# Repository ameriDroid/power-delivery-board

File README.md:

# Power Delivery board for the Indiedroid Cloud kit

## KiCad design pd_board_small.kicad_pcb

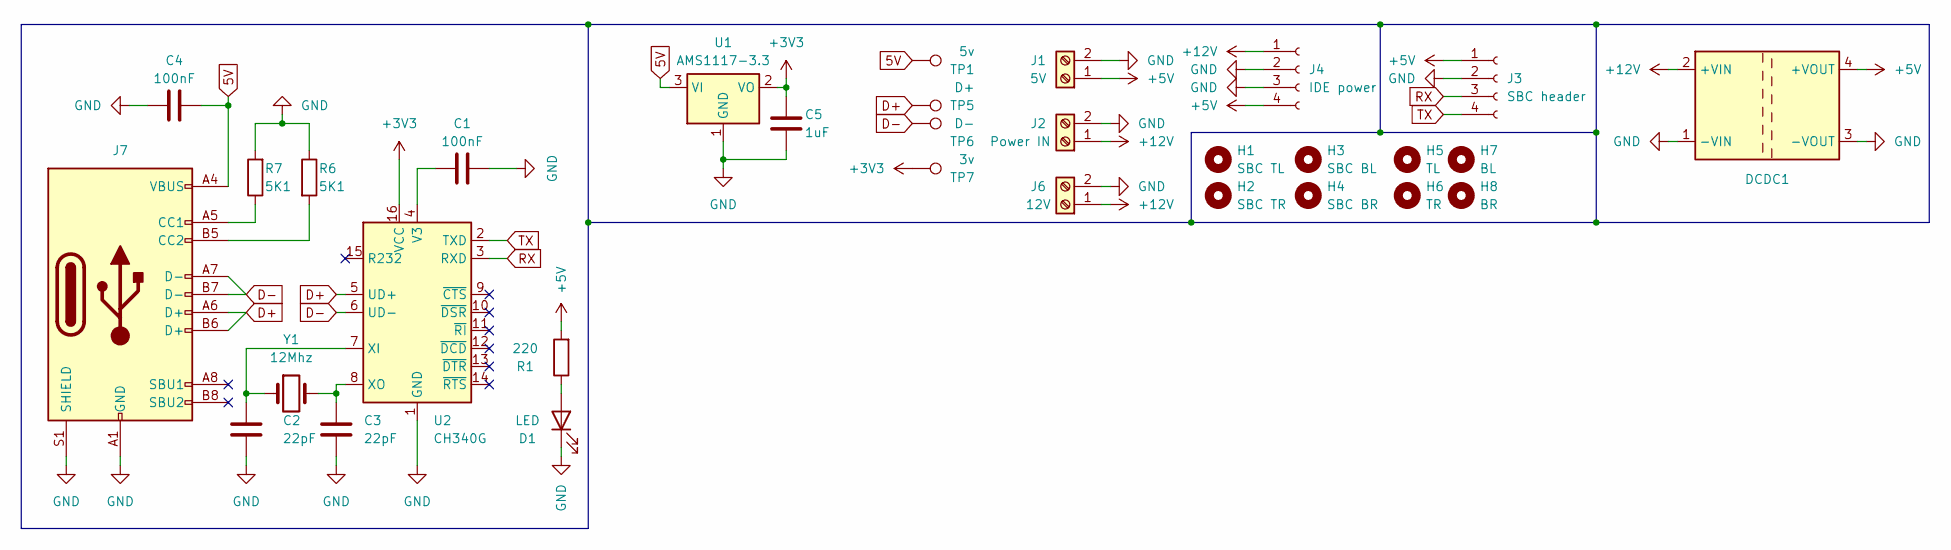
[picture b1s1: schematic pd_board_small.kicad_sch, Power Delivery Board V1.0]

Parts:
C1, C4: 100nF; C_Disc_D3.0mm_W2.0mm_P2.50mm
C2, C3: 22pF; C_Disc_D3.0mm_W2.0mm_P2.50mm
C5: 1uF; C_Disc_D3.0mm_W2.0mm_P2.50mm
D1: LED; LED_D5.0mm
DCDC1: Converter_DCDC_5_32V
H1: SBC TL; MountingHole_3.5mm
H2: SBC TR; MountingHole_3.5mm
H3: SBC BL; MountingHole_3.5mm
H4: SBC BR; MountingHole_3.5mm
H5: TL; MountingHole_3.5mm
H6: TR; MountingHole_3.5mm
H7: BL; MountingHole_3.5mm
H8: BR; MountingHole_3.5mm
J1: 5V; TerminalBlock_RND_205-00001_1x02_P5.00mm_Horizontal
J2: Power IN; TerminalBlock_RND_205-00001_1x02_P5.00mm_Horizontal
J3: SBC header; PinSocket_1x04_P2.54mm_Vertical
J4: IDE power; IDE molex 4pin
J6: 12V; TerminalBlock_RND_205-00001_1x02_P5.00mm_Horizontal
J7: USB_C_Receptacle_USB2.0_16P; USB_C_Receptacle_GCT_USB4105-xx-A_16P_TopMnt_Horizontal
R1: 220; R_Axial_DIN0204_L3.6mm_D1.6mm_P7.62mm_Horizontal
R6, R7: 5K1; R_Axial_DIN0204_L3.6mm_D1.6mm_P7.62mm_Horizontal
TP1: 5v; TestPoint_Pad_D1.5mm
TP5: D+; TestPoint_Pad_D1.5mm
TP6: D-; TestPoint_Pad_D1.5mm
TP7: 3v; TestPoint_Pad_D1.5mm
U1: AMS1117-3.3; SOT-223-3_TabPin2
U2: CH340G; SOIC-16_3.9x9.9mm_P1.27mm
Y1: 12Mhz; Crystal_HC49-4H_Vertical

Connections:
5V: C4.2, J7.A4 (VBUS), J7.A9 (VBUS), J7.B4 (VBUS), J7.B9 (VBUS), TP1.1, U1.3 (VI)
+3V3: C5.1, TP7.1, U1.2 (VO), U2.16 (VCC)
+5V: DCDC1.4 (+VOUT), J1.1, J3.1, J4.4, R1.2
+12V: DCDC1.2 (+VIN), J2.1, J4.1, J6.1
D+: J7.A6 (D+), J7.B6 (D+), TP5.1, U2.5 (UD+)
D-: J7.A7 (D-), J7.B7 (D-), TP6.1, U2.6 (UD-)
GND: C1.2, C2.1, C3.1, C4.1, C5.2, D1.1 (K), DCDC1.1 (-VIN), DCDC1.3 (-VOUT), J1.2, J2.2, J3.2, J4.2, J4.3, J6.2, J7.A1 (GND), J7.A12 (GND), J7.B1 (GND), J7.B12 (GND), J7.S1 (SHIELD), R6.1, R7.2, U1.1 (GND), U2.1 (GND)
unnamed: D1.2 (A), R1.1
unnamed: J7.A5 (CC1), R7.1
unnamed: J7.B5 (CC2), R6.2
unnamed: C1.1, U2.4 (V3)
unnamed: C2.2, U2.7 (XI), Y1.1
unnamed: C3.2, U2.8 (XO), Y1.2
RX: J3.3, U2.3 (RXD)
TX: J3.4, U2.2 (TXD)

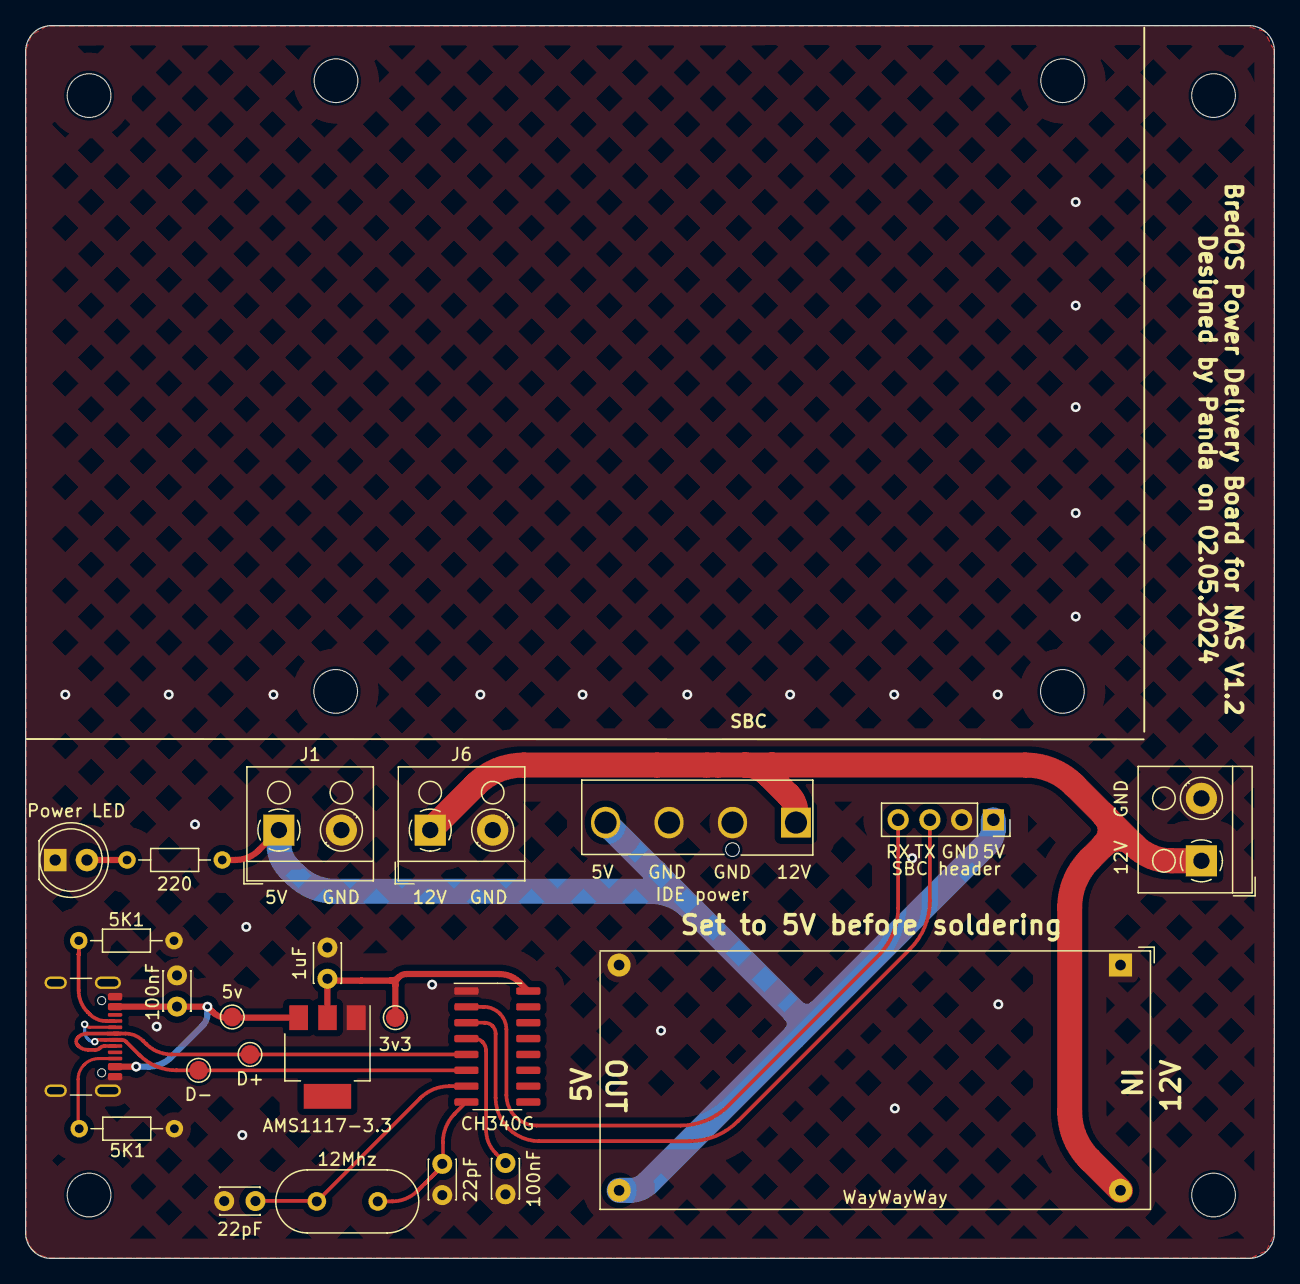
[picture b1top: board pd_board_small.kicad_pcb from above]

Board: 2 copper layers, 99.9 x 98.7 mm, 31 parts (0 on the bottom side), 15 nets.

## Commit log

2024-05-02 Add the files
